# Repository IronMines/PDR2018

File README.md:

# Projet de Recherche Majeur ISIC 2018 

Autheurs : William FREAU et Sébastien PACQUETEAU

Le programme arduino et les bibliothèques C++ ici permette de contrôler une base roulante de manière avec des commandes simples. 

Il reste à implémenter le lien I2C pour que les actions du robot ne soit plus dans le fichier stratégie, mais sur une carte dédiée plus puissante.

Lien vers le Bitbucket : [dépot privé sur le compte du club robotique](https://bitbucket.org/robotiqueIMT/coupedefrancepdr2018/src/master/)

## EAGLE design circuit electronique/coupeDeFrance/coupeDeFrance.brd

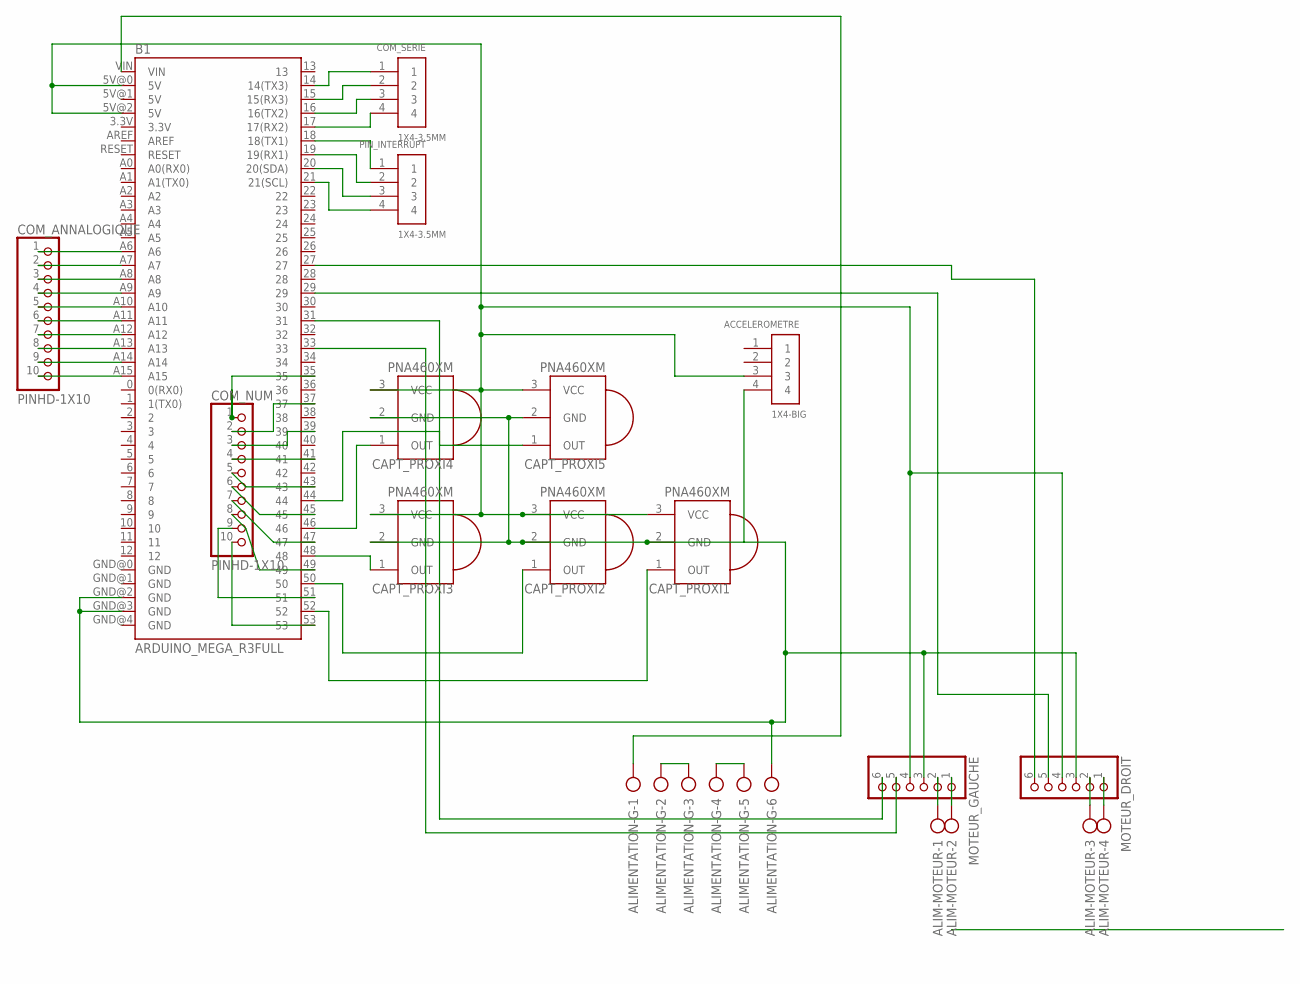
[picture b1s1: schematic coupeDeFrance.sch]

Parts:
ACCELEROMETRE: 1X4-BIG; 1X04-BIG
ALIM-MOTEUR: AK300/4
ALIMENTATION-G: AK300/6
B1: ARDUINO_MEGA_R3FULL; ARDUINO_MEGA
CAPT_PROXI1, CAPT_PROXI2, CAPT_PROXI3, CAPT_PROXI4, CAPT_PROXI5: PNA460XM
COM_ANNALOGIQUE: PINHD-1X10; 1X10-BIG
COM_NUM: PINHD-1X10; 1X10-BIG
COM_SERIE: 1X4-3.5MM; 1X04-3.5MM
MOTEUR_DROIT: PINHD-1X6; 1X06
MOTEUR_GAUCHE: PINHD-1X6; 1X06
PIN_INTERRUPT: 1X4-3.5MM; 1X04-3.5MM

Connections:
unnamed: ACCELEROMETRE.3, B1.5V@0 (5V), B1.5V@2 (5V), CAPT_PROXI1.3 (VCC), CAPT_PROXI2.3 (VCC), CAPT_PROXI3.3 (VCC), CAPT_PROXI4.3 (VCC), CAPT_PROXI5.3 (VCC), MOTEUR_DROIT.4, MOTEUR_GAUCHE.4
unnamed: B1.A15, COM_ANNALOGIQUE.10
unnamed: B1.52, CAPT_PROXI1.1 (OUT)
unnamed: B1.50, CAPT_PROXI2.1 (OUT)
unnamed: B1.48, CAPT_PROXI3.1 (OUT)
unnamed: B1.46, CAPT_PROXI4.1 (OUT)
unnamed: B1.44, CAPT_PROXI5.1 (OUT)
unnamed: B1.A12, COM_ANNALOGIQUE.7
unnamed: ALIMENTATION-G.2, ALIMENTATION-G.3
unnamed: ALIMENTATION-G.4, ALIMENTATION-G.5
unnamed: ALIM-MOTEUR.1, MOTEUR_GAUCHE.2
unnamed: ALIM-MOTEUR.2, MOTEUR_GAUCHE.1
unnamed: ALIM-MOTEUR.3, MOTEUR_DROIT.2
unnamed: ALIMENTATION-G.1, B1.VIN
unnamed: B1.A11, COM_ANNALOGIQUE.6
unnamed: B1.A14, COM_ANNALOGIQUE.9
unnamed: B1.A13, COM_ANNALOGIQUE.8
unnamed: B1.A10, COM_ANNALOGIQUE.5
unnamed: B1.A9, COM_ANNALOGIQUE.4
unnamed: B1.A8, COM_ANNALOGIQUE.3
unnamed: B1.A7, COM_ANNALOGIQUE.2
unnamed: B1.A6, COM_ANNALOGIQUE.1
unnamed: B1.53, COM_NUM.10
unnamed: B1.51, COM_NUM.9
unnamed: B1.49, COM_NUM.8
unnamed: B1.47, COM_NUM.7
unnamed: B1.45, COM_NUM.6
unnamed: B1.43, COM_NUM.5
unnamed: B1.41, COM_NUM.4
unnamed: B1.39, COM_NUM.3
unnamed: B1.37, COM_NUM.2
unnamed: B1.35, COM_NUM.1
unnamed: B1.14 (14(TX3)), COM_SERIE.1
unnamed: B1.15 (15(RX3)), COM_SERIE.2
unnamed: B1.16 (16(TX2)), COM_SERIE.3
unnamed: B1.17 (17(RX2)), COM_SERIE.4
unnamed: B1.18 (18(TX1)), PIN_INTERRUPT.1
unnamed: B1.19 (19(RX1)), PIN_INTERRUPT.2
unnamed: B1.20 (20(SDA)), PIN_INTERRUPT.3
unnamed: B1.21 (21(SCL)), PIN_INTERRUPT.4
unnamed: B1.33, MOTEUR_GAUCHE.5
unnamed: B1.31, MOTEUR_GAUCHE.6
unnamed: B1.29, MOTEUR_DROIT.5
unnamed: B1.27, MOTEUR_DROIT.6
unnamed: ALIM-MOTEUR.4, MOTEUR_DROIT.1
unnamed: ACCELEROMETRE.4, ALIMENTATION-G.6, B1.GND@2 (GND), B1.GND@3 (GND), CAPT_PROXI1.2 (GND), CAPT_PROXI2.2 (GND), CAPT_PROXI3.2 (GND), CAPT_PROXI4.2 (GND), CAPT_PROXI5.2 (GND), MOTEUR_DROIT.3, MOTEUR_GAUCHE.3

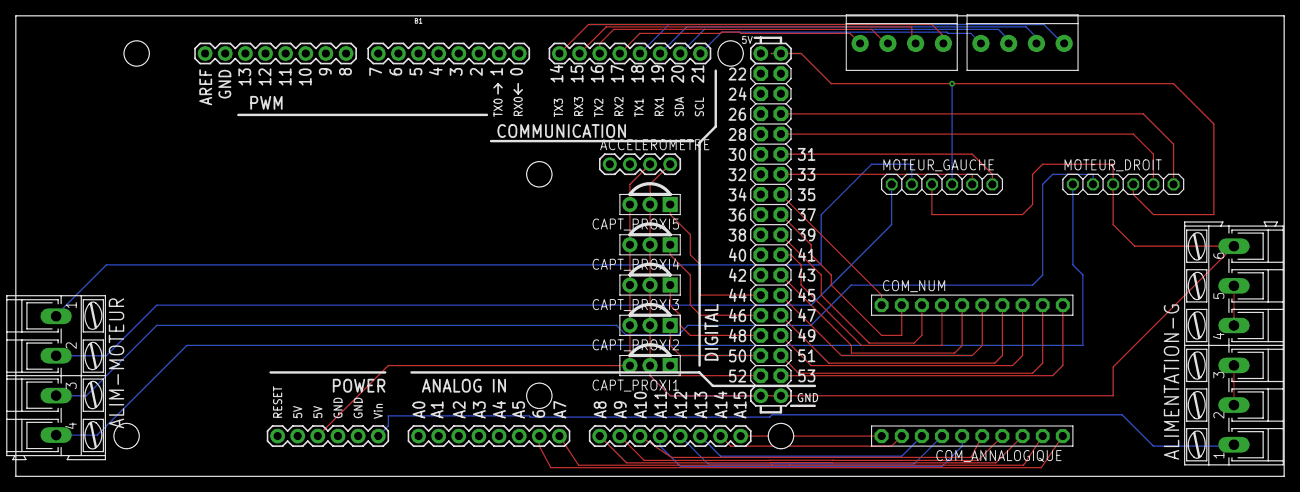
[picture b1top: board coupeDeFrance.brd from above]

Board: 2 copper layers, 160.0 x 58.1 mm, 15 parts (0 on the bottom side), 46 nets.

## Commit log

2018-11-24 Ajout du projet PDR2018
    Ce code Arduino permet de contrôler une base roulante via une API
2018-11-24 Update README.md
    Description du projet
2018-11-24 Export de la documentation en pdf
    Et suppression d'un dossier zip inutile

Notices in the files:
parts and their libraries:
SparkFun-Boards: Licensing: Creative Commons ShareAlike 4.0 International - https://creativecommons.org/licenses/by-sa/4.0
